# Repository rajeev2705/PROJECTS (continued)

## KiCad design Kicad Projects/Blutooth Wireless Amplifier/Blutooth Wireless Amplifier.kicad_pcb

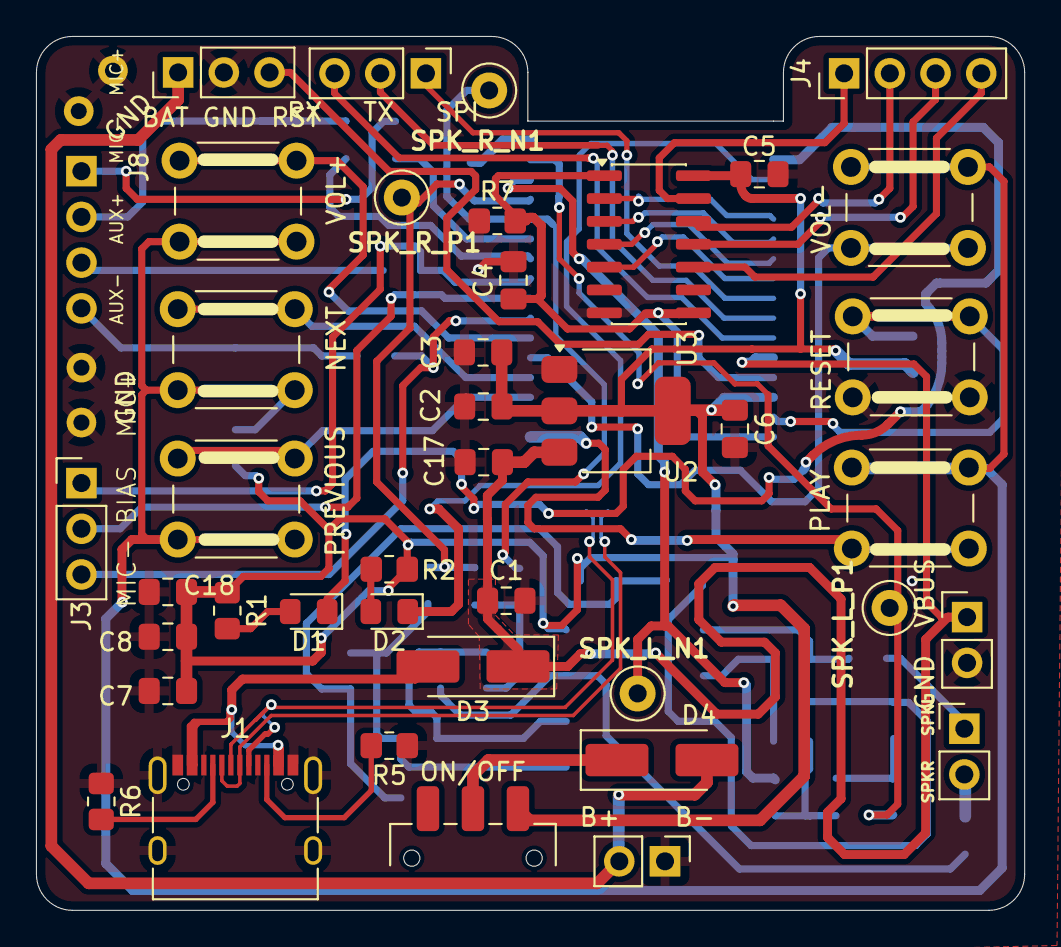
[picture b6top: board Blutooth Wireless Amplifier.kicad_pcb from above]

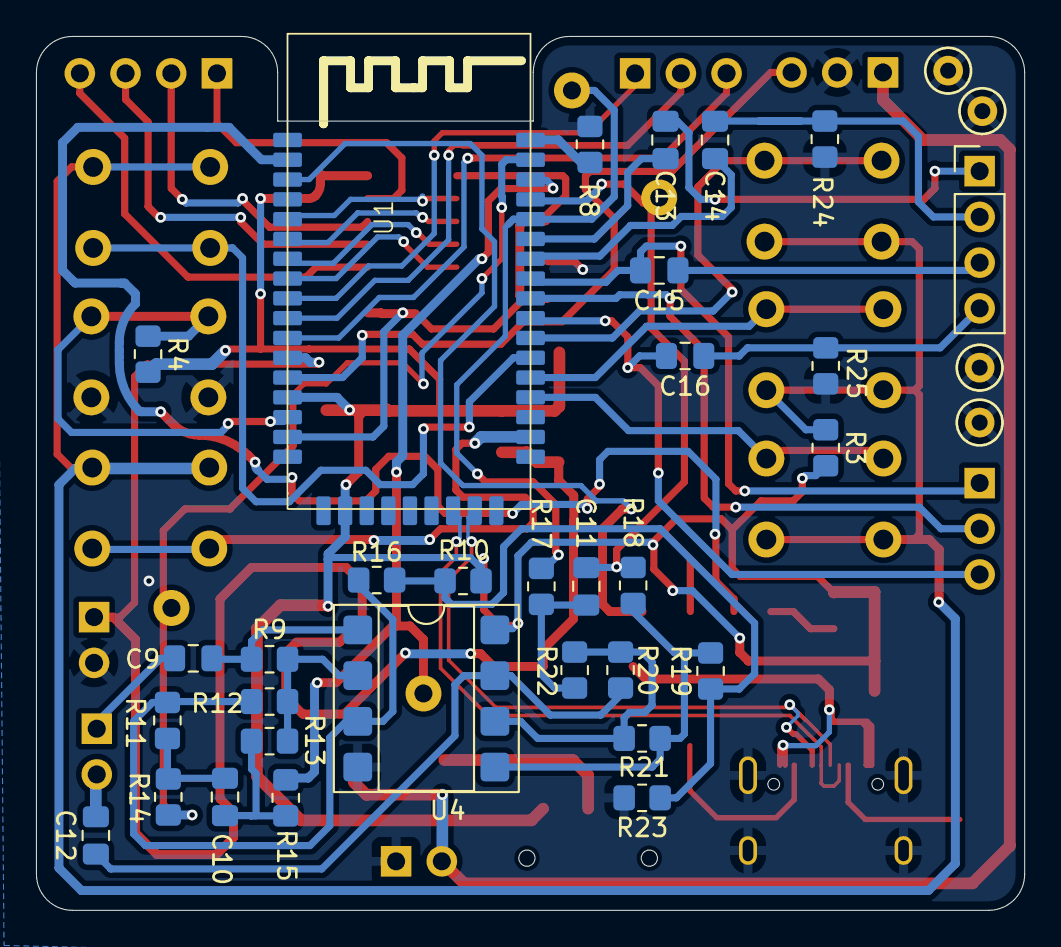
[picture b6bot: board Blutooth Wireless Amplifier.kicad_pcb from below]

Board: 2 copper layers, 54.9 x 48.5 mm, 75 parts (35 on the bottom side), 60 nets.

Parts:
B+    B-: Conn_01x02_Socket; PinHeader_1x02_P2.54mm_Vertical
BAT GND RST: Conn_01x03_Socket; PinHeader_1x03_P2.54mm_Vertical
C1: 0.1UF; C_0805_2012Metric_Pad1.18x1.45mm_HandSolder
C2, C3, C8, C10, C17, C18: 0.1uF; C_0805_2012Metric_Pad1.18x1.45mm_HandSolder
C4, C12: 0.1uf; C_0805_2012Metric_Pad1.18x1.45mm_HandSolder
C5, C6: 10uf; C_0805_2012Metric_Pad1.18x1.45mm_HandSolder
C7, C9, C11, C13, C14, C15, C16: 10uF; C_0805_2012Metric_Pad1.18x1.45mm_HandSolder
D1, D2: LED; LED_0805_2012Metric_Pad1.15x1.40mm_HandSolder
D3, D4: SS14; D_SMA_Handsoldering
GND: TestPoint; TestPoint_WireHole
GND  VBUS  : Conn_01x02_Socket; PinHeader_1x02_P2.54mm_Vertical
GND#2: TestPoint; TestPoint_WireHole
J1: USB_C_Receptacle_USB2.0_16P; USB_C_Receptacle_XKB_U262-16XN-4BVC11
J3: Conn_01x03_Socket; PinHeader_1x03_P2.54mm_Vertical
J4, J8: Conn_01x04_Socket; PinHeader_1x04_P2.54mm_Vertical
NEXT: SW_Push; SW_PUSH_6mm_H4.3mm
ON/OFF: SW_SPDT; SW_SPDT_CK_JS102011SAQN
PLAY: SW_Push; SW_PUSH_6mm_H4.3mm
PREVIOUS: SW_Push; SW_PUSH_6mm_H4.3mm
R1, R2: 2k; R_0805_2012Metric_Pad1.20x1.40mm_HandSolder
R3, R4, R7, R9, R10, R11, R12, R13, R16, R18, R19, R20, R21, R22, R23: 10K; R_0805_2012Metric_Pad1.20x1.40mm_HandSolder
R5, R6: 5.1K; R_0805_2012Metric_Pad1.20x1.40mm_HandSolder
R8, R14, R15, R17, R24, R25: 0R; R_0805_2012Metric_Pad1.20x1.40mm_HandSolder
RESET: SW_Push; SW_PUSH_6mm_H4.3mm
RX   TX   SPI: Conn_01x03_Pin; PinHeader_1x03_P2.54mm_Vertical
SPKR   SPKL: Conn_01x02_Socket; PinHeader_1x02_P2.54mm_Vertical
SPK_L_N1: TestPoint_Loop_D1.80mm_Drill1.0mm_Beaded
SPK_L_P1: TestPoint_Loop_D1.80mm_Drill1.0mm_Beaded
SPK_R_N1: TestPoint_Loop_D1.80mm_Drill1.0mm_Beaded
SPK_R_P1: TestPoint_Loop_D1.80mm_Drill1.0mm_Beaded
TP1, TP3: TestPoint; TestPoint_WireHole
U1: Untitled
U2: AMS1117-3.3; SOT-223-3_TabPin2
U3: TXS0104ED; SOIC-14_3.9x8.7mm_P1.27mm
U4: LM358; DIP-8_W7.62mm_SMDSocket_SmallPads
VOL+: SW_Push; SW_PUSH_6mm_H4.3mm
VOL-: SW_Push; SW_PUSH_6mm_H4.3mm

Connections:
1.8V: C4.1, R7.2 (-), U1.A16 (1.8V), U3.1 (V_{CCA}), U3.8 (OE)
/VCC: C2.1, C3.1, C5.1, C6.1, C7.1, C8.1, C18.1, ON/OFF.3 (C), R1.1 (+), R2.1 (+), R3.2 (-), R4.2 (-), R10.1 (+), U1.A14 (BAT), U1.A19 (BAT_SENSE), U2.2 (VO), U3.14 (V_{CCB}), U4.8 (V+)
/VREF: R10.2 (-), R16.1 (+), R19.1 (+), R23.1 (+)
/bat: B+ B-.2, BAT GND RST.1, D4.2 (A)
CC1: J1.A5 (CC1), R6.2 (-)
CC2: J1.B5 (CC2), R5.2 (-)
CLK: U1.A7 (CLK), U3.4 (A3)
CSB: U1.A6 (CSB), U3.3 (A2)
D+: J1.A6 (D+), J1.B6 (D+), U1.A25 (USB_P)
D-: J1.A7 (D-), J1.B7 (D-), U1.A24 (USB_N)
GND: B+ B-.1, BAT GND RST.2, C1.2, C2.2, C3.2, C4.2, C5.2, C6.2, C7.2, C8.2, C17.2, C18.2, GND.1, GND VBUS.2, GND#2.1, J1.A1 (GND), J1.A8 (SBU1), J1.A12 (GND), J1.B1 (GND), J1.B8 (SBU2), J1.B12 (GND), J1.S1 (SHIELD), R5.1 (+), R6.1 (+), R7.1 (+), R8.1 (+), R23.2 (-), R24.2 (-), R25.2 (-), RESET.1, TP1.1, TP3.1, U2.1 (GND), U3.7 (GND), U4.4 (V-)
MIC_AN: C16.2, J3.3, U1.A34 (MIC_AN)
MIC_AP: C15.2, J3.1, U1.A36 (MIC_AP)
MIC_BIAS: J3.2, U1.A35 (MIC_BIAS)
MIC_BN: C14.2, U1.A37 (MIC_BN)
MISO: U1.A5 (MISO), U3.2 (A1)
MOSI: U1.A8 (MOSI), U3.5 (A4)
unnamed: D1.2 (A), R1.2 (-)
unnamed: D1.1 (K), U1.A2 (LED1)
unnamed: D2.2 (A), R2.2 (-)
unnamed: D2.1 (K), U1.A3 (LED0)
unnamed: D3.2 (A), J1.A4 (VBUS), J1.A9 (VBUS), J1.B4 (VBUS), J1.B9 (VBUS)
unnamed: D4.1 (K), ON/OFF.2 (B)
unnamed: C13.1, J8.1
unnamed: C14.1, J8.2, R24.1 (+)
unnamed: C15.1, J8.3
unnamed: C16.1, J8.4, R25.1 (+)
unnamed: NEXT.2, PLAY.2, PREVIOUS.2, R3.1 (+), VOL+.2, VOL-.2
unnamed: R4.1 (+), RESET.2, U1.A15 (POWER_EN)
unnamed: R8.2 (-), U1.A43 (RFOUT)
unnamed: C9.1, R9.1 (+), U4.1
unnamed: R11.1 (+), R12.2 (-), R16.2 (-), U4.3 (+)
unnamed: C10.2, R11.2 (-), R14.1 (+)
unnamed: R9.2 (-), R12.1 (+), R13.1 (+), U4.2 (-)
unnamed: C10.1, R13.2 (-), R15.1 (+)
unnamed: C11.1, R17.1 (+), R20.2 (-)
unnamed: R18.1 (+), R19.2 (-), R21.2 (-), U4.5 (+)
unnamed: R20.1 (+), R21.1 (+), R22.2 (-), U4.6 (-)
unnamed: C12.1, R22.1 (+), U4.7
unnamed: PLAY.1, U1.A28 (PIO7)
unnamed: PREVIOUS.1, U1.A30 (PIO18)
unnamed: NEXT.1, U1.A31 (PIO19)
unnamed: U1.A33 (VOL+), VOL+.1
unnamed: U1.A32 (VOL-), VOL-.1
RST: BAT GND RST.3, U1.A13 (RST)
RX: RX TX SPI.3, U1.A11 (RX)
SCK: J4.3, U3.11 (B3)
SD_DOUT: J4.1, U3.13 (B1)
SD_IN: J4.4, U3.10 (B4)
SPI: RX TX SPI.1, U1.A9 (SPI)
SPK_L_N1: R15.2 (-), SPK_L_N1.1, U1.A41 (SPK_L_N1)
SPK_L_P1: R14.2 (-), SPK_L_P1.1, U1.A42 (SPK_L_P1)
SPK_R_N1: R17.2 (-), SPK_R_N1.1, U1.A39 (SPK_R_N1)
SPK_R_P1: C11.2, R18.2 (-), SPK_R_P1.1, U1.A40 (SPK_R_P1)
TX: RX TX SPI.2, U1.A10 (TX)
USB_5V: C1.1, C17.1, D3.1 (K), GND VBUS.1, U1.A12 (VBUS), U2.3 (VI)
WS: J4.2, U3.12 (B2)
_MIC_BP: C13.2, U1.A38 (_MIC_BP)
spk_R: C12.2, SPKR SPKL.2
spk_l: C9.2, SPKR SPKL.1

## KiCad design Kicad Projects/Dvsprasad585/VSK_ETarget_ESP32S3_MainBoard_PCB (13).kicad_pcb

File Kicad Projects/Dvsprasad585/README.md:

# ?? Confidential Client Project

The source code, KiCad design files (PCB, Schematic, Project files), and firmware for this project are strictly confidential. They are not permitted by the client to be shared publicly. 

Only portfolio representations such as PDFs, images, and 3D renders are included in this repository for demonstration purposes.

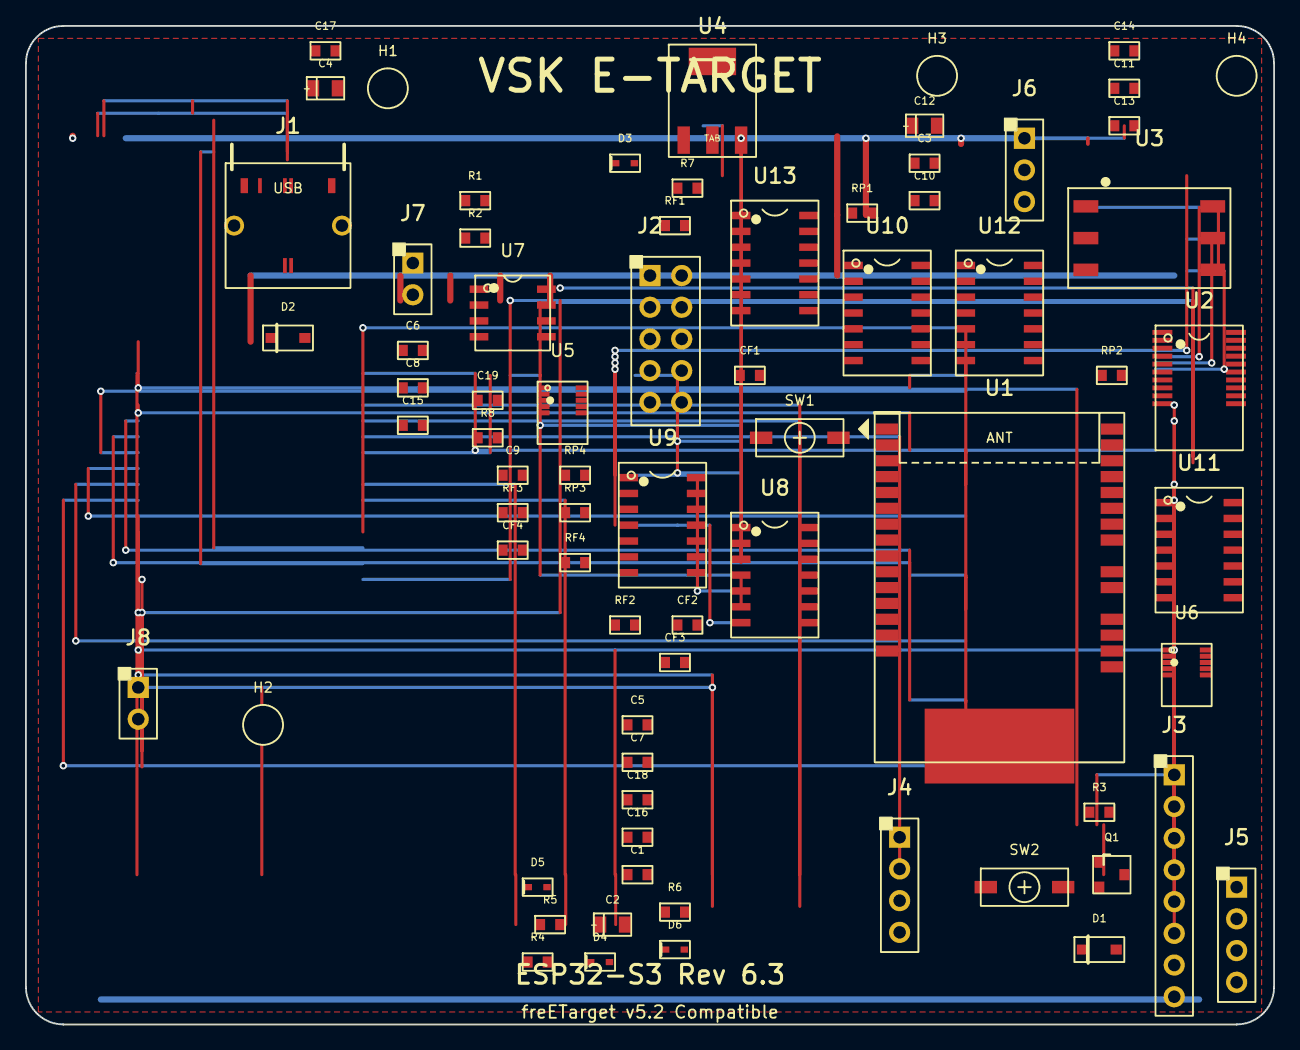
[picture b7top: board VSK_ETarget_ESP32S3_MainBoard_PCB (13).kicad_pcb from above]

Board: 2 copper layers, 100.0 x 80.0 mm, 73 parts (0 on the bottom side), 43 nets.

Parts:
C1: 100nF ESP32; C_0603_1608Metric
C2: 10uF 3V3; C_0805_2012Metric
C3: 100nF LDO In; C_0603_1608Metric
C4: 22uF LDO Out; C_0805_2012Metric
C5: 100nF FT231; C_0603_1608Metric
C6: 100nF ADS0x48; C_0603_1608Metric
C7: 100nF ADS0x49; C_0603_1608Metric
C8: 100nF LM75; C_0603_1608Metric
C9: 100nF VREF; C_0603_1608Metric
C10: 100nF DCDC In; C_0603_1608Metric
C11: 100nF ISO Out; C_0603_1608Metric
C12: 10uF 5V; C_0805_2012Metric
C13: 100nF LM339#1; C_0603_1608Metric
C14: 100nF LM339#2; C_0603_1608Metric
C15: 100nF 74HC74#1; C_0603_1608Metric
C16: 100nF 74HC74#2; C_0603_1608Metric
C17: 100nF 74HC74#3; C_0603_1608Metric
C18: 100nF 74HC74#4; C_0603_1608Metric
C19: 100nF VREF RC; C_0603_1608Metric
CF1, CF2, CF3, CF4: 10nF Slope; C_0603_1608Metric
D1: 1N4148W; D_SOD-123
D2: PRTR5V0U2X ESD; D_SOD-123
D3: PWR LED; LED_0603_1608Metric
D4: RDY Green; LED_0603_1608Metric
D5: X Red; LED_0603_1608Metric
D6: Y Yellow; LED_0603_1608Metric
H1, H2, H3, H4: MH; MountingHole_3.2mm_M3
J1: USB-C; USB_C_Receptacle_GCT_USB4085
J2: FRC 10-pin SENSOR; PinHeader_2x05_P2.54mm_Vertical
J3: MOTOR/LED; PinHeader_1x08_P2.54mm_Vertical
J4: AUX SERIAL; PinHeader_1x04_P2.54mm_Vertical
J5: RAPID FIRE; PinHeader_1x04_P2.54mm_Vertical
J6: FACE SENSOR; PinHeader_1x03_P2.54mm_Vertical
J7, J8: MFS; PinHeader_1x02_P2.54mm_Vertical
Q1: 2N7002; SOT-23
R1, R2: 4K7 I2C; R_0603_1608Metric
R3: 1K MOTOR; R_0603_1608Metric
R4, R5, R6: 330R LED; R_0603_1608Metric
R7: 1K PWR; R_0603_1608Metric
R8: 10K VREF; R_0603_1608Metric
RF1, RF2, RF3, RF4: 10K Slope; R_0603_1608Metric
RP1, RP2, RP3, RP4: 10K PU; R_0603_1608Metric
SW1: RESET; SW_SPST_TL3342
SW2: BOOT; SW_SPST_TL3342
U1: ESP32-S3-WROOM-1
U2: FT231XS; SSOP-20_3.9x8.7mm_P0.635mm
U3: A0505XT-1WR3-TR; Converter_DCDC_MORNSUN_A0505XT
U4: AMS1117-3.3; SOT-223-3_TabPin2
U5: ADS1115 (0x48); MSOP-10_3x3mm_P0.5mm
U6: ADS1115 (0x49); MSOP-10_3x3mm_P0.5mm
U7: LM75 (0x4F); SOIC-8_3.9x4.9mm_P1.27mm
U8: LM339 #1 N/E; SOIC-14_3.9x8.7mm_P1.27mm
U9: LM339 #2 S/W; SOIC-14_3.9x8.7mm_P1.27mm
U10: 74HC74 NORTH; SOIC-14_3.9x8.7mm_P1.27mm
U11: 74HC74 EAST; SOIC-14_3.9x8.7mm_P1.27mm
U12: 74HC74 SOUTH; SOIC-14_3.9x8.7mm_P1.27mm
U13: 74HC74 WEST; SOIC-14_3.9x8.7mm_P1.27mm

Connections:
+3V3: C1.1, C2.1, C4.1, C5.1, C6.1, C7.1, C8.1, C15.1, C16.1, C17.1, C18.1, J4.3, J5.3, J6.2, R1.1, R2.1, R4.2, R5.2, R6.2, R7.1, RP1.1, RP2.1, RP3.1, RP4.1, U1.2, U2.4, U4.2, U4.4, U5.10, U6.6, U6.10, U7.5, U7.6, U7.7, U7.8, U10.2, U10.4, U10.10, U10.13, U10.14, U11.2, U11.4, U11.10, U11.13, U11.14, U12.2, U12.4, U12.10, U12.13, U12.14, U13.2, U13.4, U13.10, U13.13, U13.14
+5V: C3.1, C10.1, C12.1, D1.1, J1.A4, J3.7, U2.19, U2.20, U3.1, U4.3
+5V_ISO: C11.1, C13.1, C14.1, J2.2, J2.4, U3.6, U8.3, U9.3
-5V_ISO: J2.8, U3.4
AUX_RX: J4.2, SW2.1, U1.27
AUX_TX: J4.1, U1.12
COMP_E: RP2.2, U1.5, U8.1, U11.3
COMP_N: RP1.2, U1.4, U8.2, U10.3
COMP_S: RP3.2, U1.6, U9.2, U12.3
COMP_W: RP4.2, U1.7, U9.1, U13.3
EN: SW1.1, U1.3
FACE_SENSOR: J6.1, U1.19
FILT_E: CF2.1, RF2.2, U8.7
FILT_N: CF1.1, RF1.2, U8.5
FILT_S: CF3.1, RF3.2, U9.5
FILT_W: CF4.1, RF4.2, U9.7
GND: C1.2, C2.2, C3.2, C4.2, C5.2, C6.2, C7.2, C8.2, C9.2, C10.2, C11.2, C12.2, C13.2, C14.2, C15.2, C16.2, C17.2, C18.2, C19.2, CF1.2, CF2.2, CF3.2, CF4.2, D3.2, D4.2, D5.2, D6.2, H1.1, H2.1, H3.1, H4.1, J1.A1, J1.A12, J1.S1, J1.S2, J2.6, J2.10, J3.8, J4.4, J5.4, J6.3, J7.2, J8.2, Q1.2, SW1.2, SW2.2, U1.1, U1.GND, U2.6, U2.17, U3.2, U3.3, U3.5, U4.1, U5.5, U5.6, U6.5, U7.4, U8.8, U8.9, U8.10, U8.11, U8.12, U9.8, U9.9, U9.10, U9.11, U9.12, U10.7, U10.11, U10.12, U11.7, U11.11, U11.12, U12.7, U12.11, U12.12, U13.7, U13.11, U13.12
LATCH_CLR: U1.33, U10.1, U11.1, U12.1, U13.1
LED_RDY: D4.1, J3.2, R4.1, U1.24
LED_X: D5.1, J3.3, R5.1, U1.25
LED_Y: D6.1, J3.4, R6.1, U1.26
MOTOR_DRV: D1.2, J3.1, Q1.1, Q1.3, R3.2
PAPER: R3.1, U1.16
PWR_LED: D3.1, R7.2
RAPID_GREEN: J3.6, J5.2, U1.18
RAPID_RED: J3.5, J5.1, U1.17
RUN_E: U1.9, U11.5
RUN_N: U1.8, U10.5
RUN_S: U1.10, U12.5
RUN_W: U1.11, U13.5
SCL: R2.2, U1.37, U5.8, U6.8, U7.2
SDA: R1.2, U1.36, U5.9, U6.9, U7.1
SENSOR_E: J2.3, RF2.1, U5.2
SENSOR_N: J2.1, RF1.1, U5.1
SENSOR_S: J2.5, RF3.1, U5.3
SENSOR_W: J2.7, RF4.1, U5.4
UART_RX: U1.35, U2.5
UART_TX: U1.34, U2.1
USB_DM: D2.2, J1.A7, J1.B8, U1.13, U2.15
USB_DP: D2.1, J1.A6, J1.B9, U1.14, U2.16
VREF: U1.15, U6.1
VREF_FILT: C9.1, J2.9, R8.2, U8.4, U8.6, U9.4, U9.6
VREF_PWM: C19.1, R8.1, U1.20

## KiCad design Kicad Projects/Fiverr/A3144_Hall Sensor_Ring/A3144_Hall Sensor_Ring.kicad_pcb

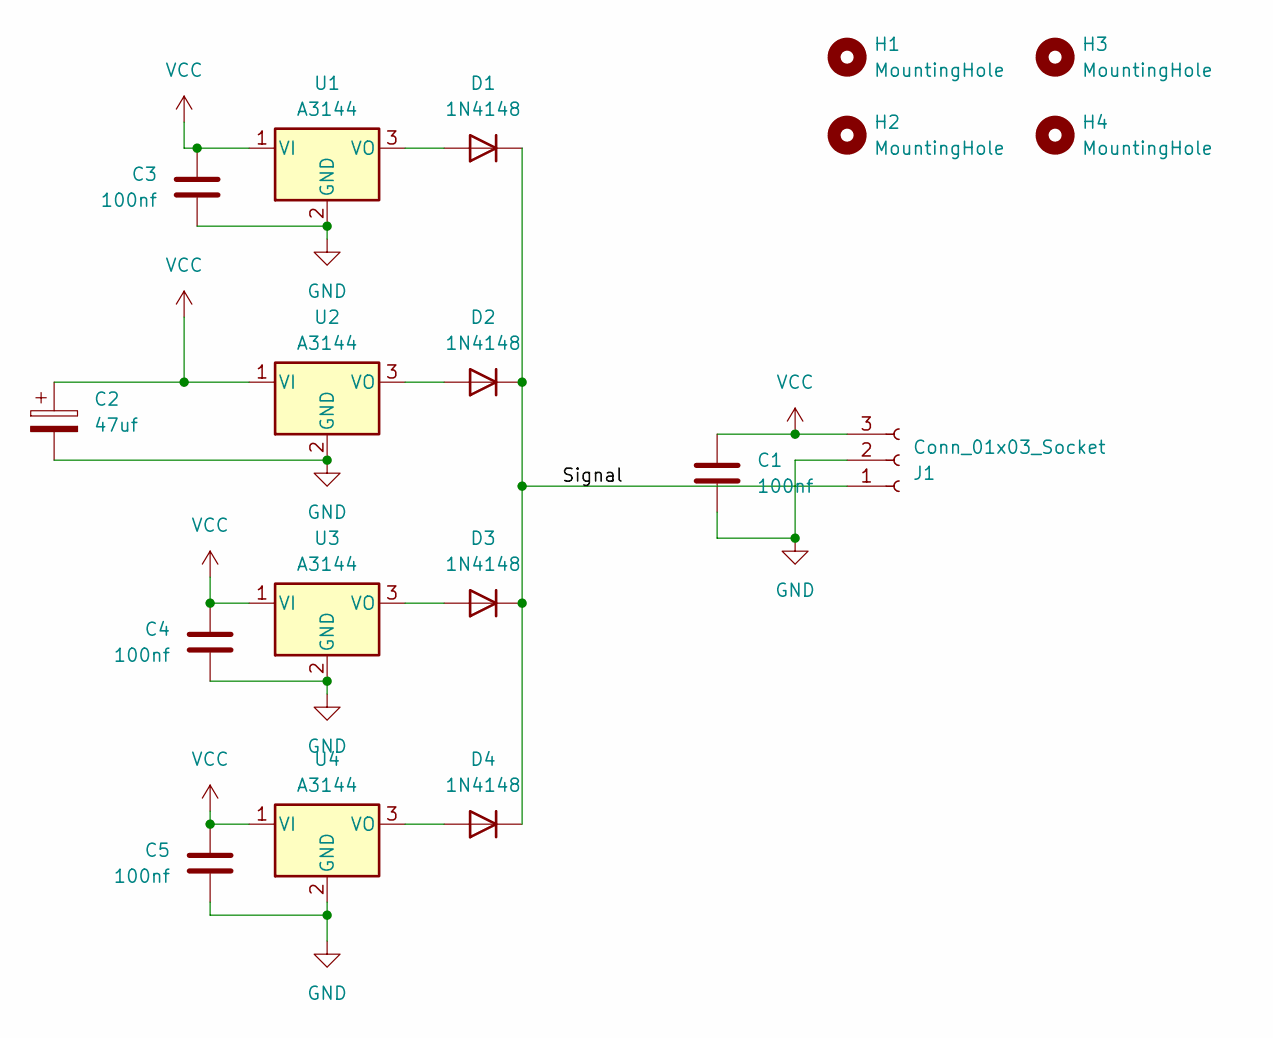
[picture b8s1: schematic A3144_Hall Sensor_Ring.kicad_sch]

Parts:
C1, C3, C4, C5: 100nf; C_Disc_D3.0mm_W1.6mm_P2.50mm
C2: 47uf; CP_Radial_D5.0mm_P2.50mm
D1, D2, D3, D4: 1N4148; D_DO-35_SOD27_P7.62mm_Horizontal
H1, H2, H3, H4: MountingHole; MountingHole_5.5mm
J1: Conn_01x03_Socket; JST_EH_S3B-EH_1x03_P2.50mm_Horizontal
U1, U2, U3, U4: A3144; TO-92_Inline new

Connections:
/Signal: D1.1 (K), D2.1 (K), D3.1 (K), D4.1 (K), J1.1
GND: C1.2, C2.2, C3.2, C4.2, C5.2, J1.2, U1.2 (GND), U2.2 (GND), U3.2 (GND), U4.2 (GND)
unnamed: D1.2 (A), U1.3 (VO)
unnamed: D2.2 (A), U2.3 (VO)
unnamed: D3.2 (A), U3.3 (VO)
unnamed: D4.2 (A), U4.3 (VO)
VCC: C1.1, C2.1, C3.1, C4.1, C5.1, J1.3, U1.1 (VI), U2.1 (VI), U3.1 (VI), U4.1 (VI)

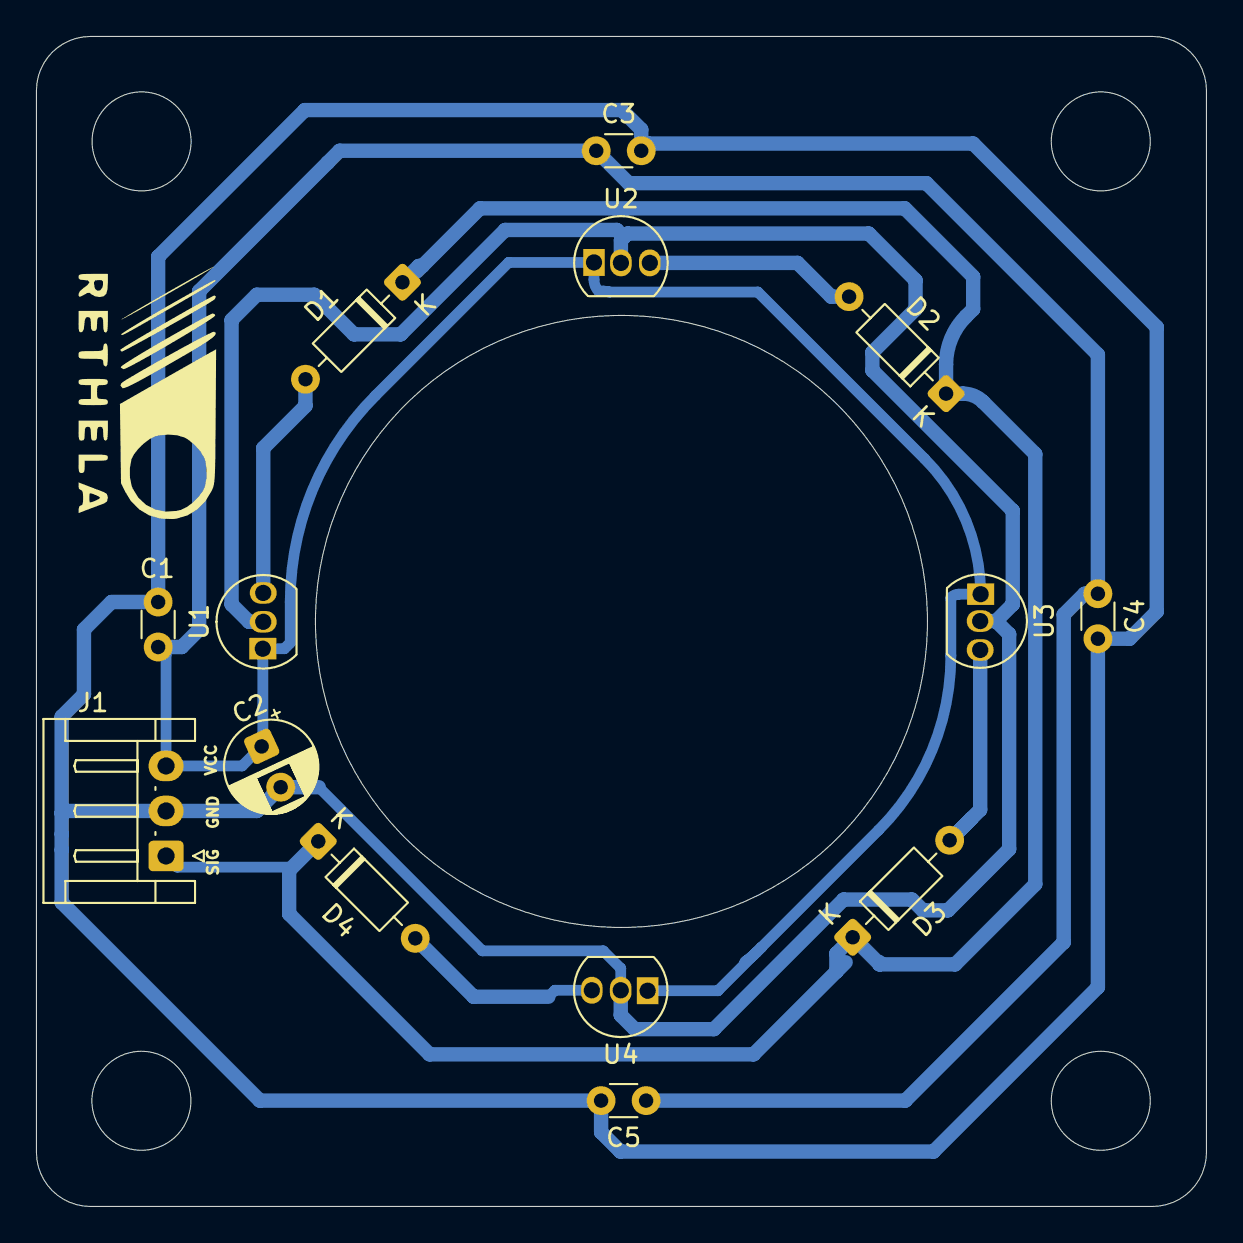
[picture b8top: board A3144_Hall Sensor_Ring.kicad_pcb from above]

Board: 2 copper layers, 65.0 x 65.0 mm, 18 parts (0 on the bottom side), 7 nets.
